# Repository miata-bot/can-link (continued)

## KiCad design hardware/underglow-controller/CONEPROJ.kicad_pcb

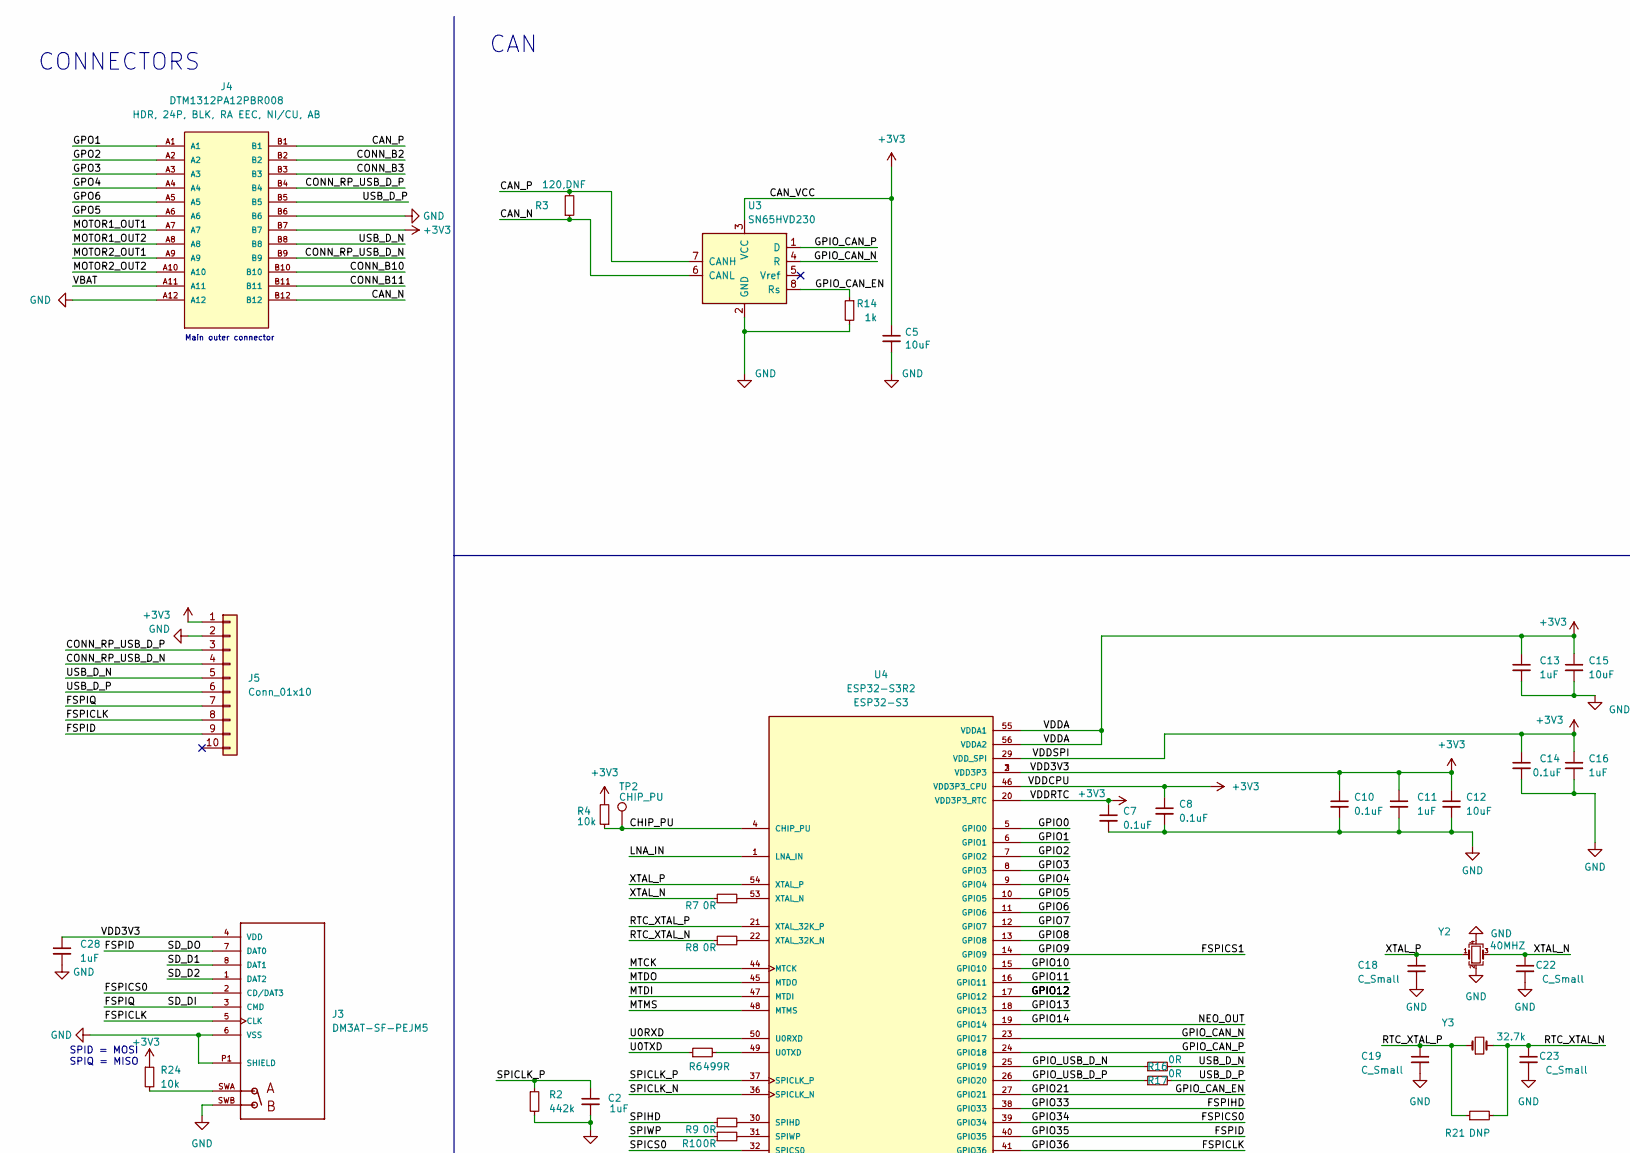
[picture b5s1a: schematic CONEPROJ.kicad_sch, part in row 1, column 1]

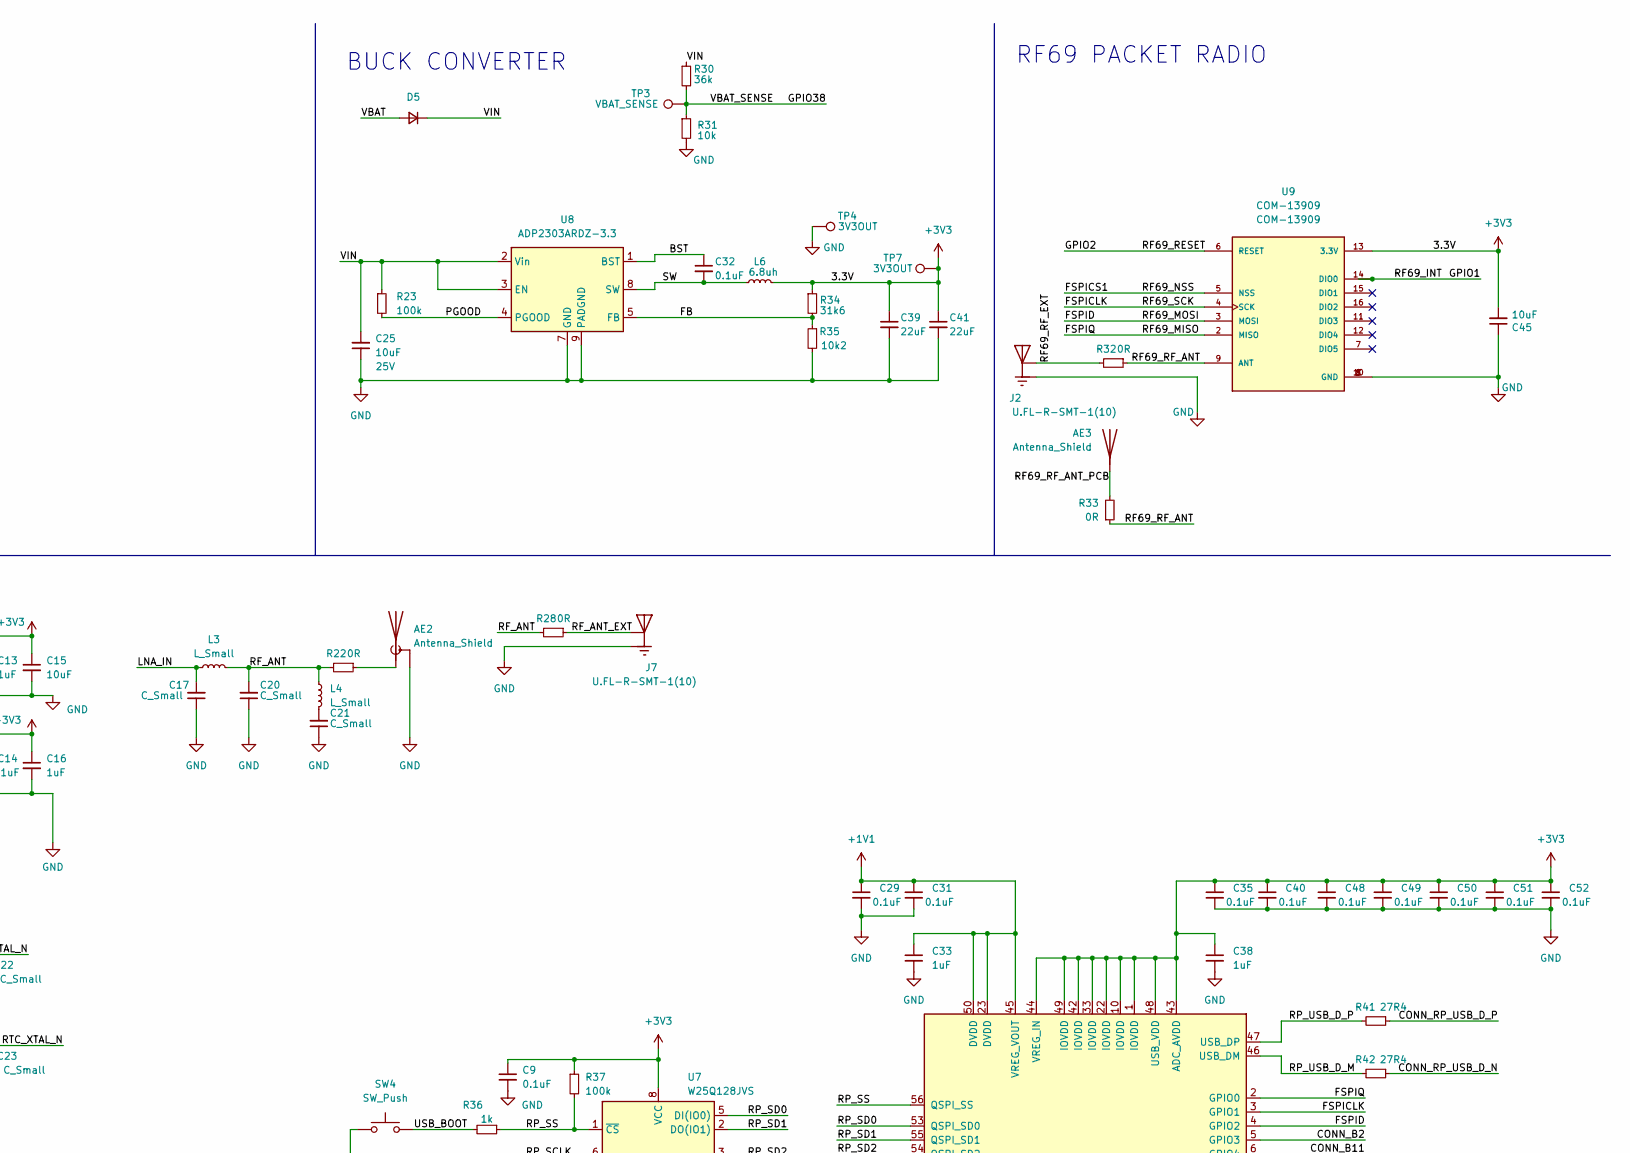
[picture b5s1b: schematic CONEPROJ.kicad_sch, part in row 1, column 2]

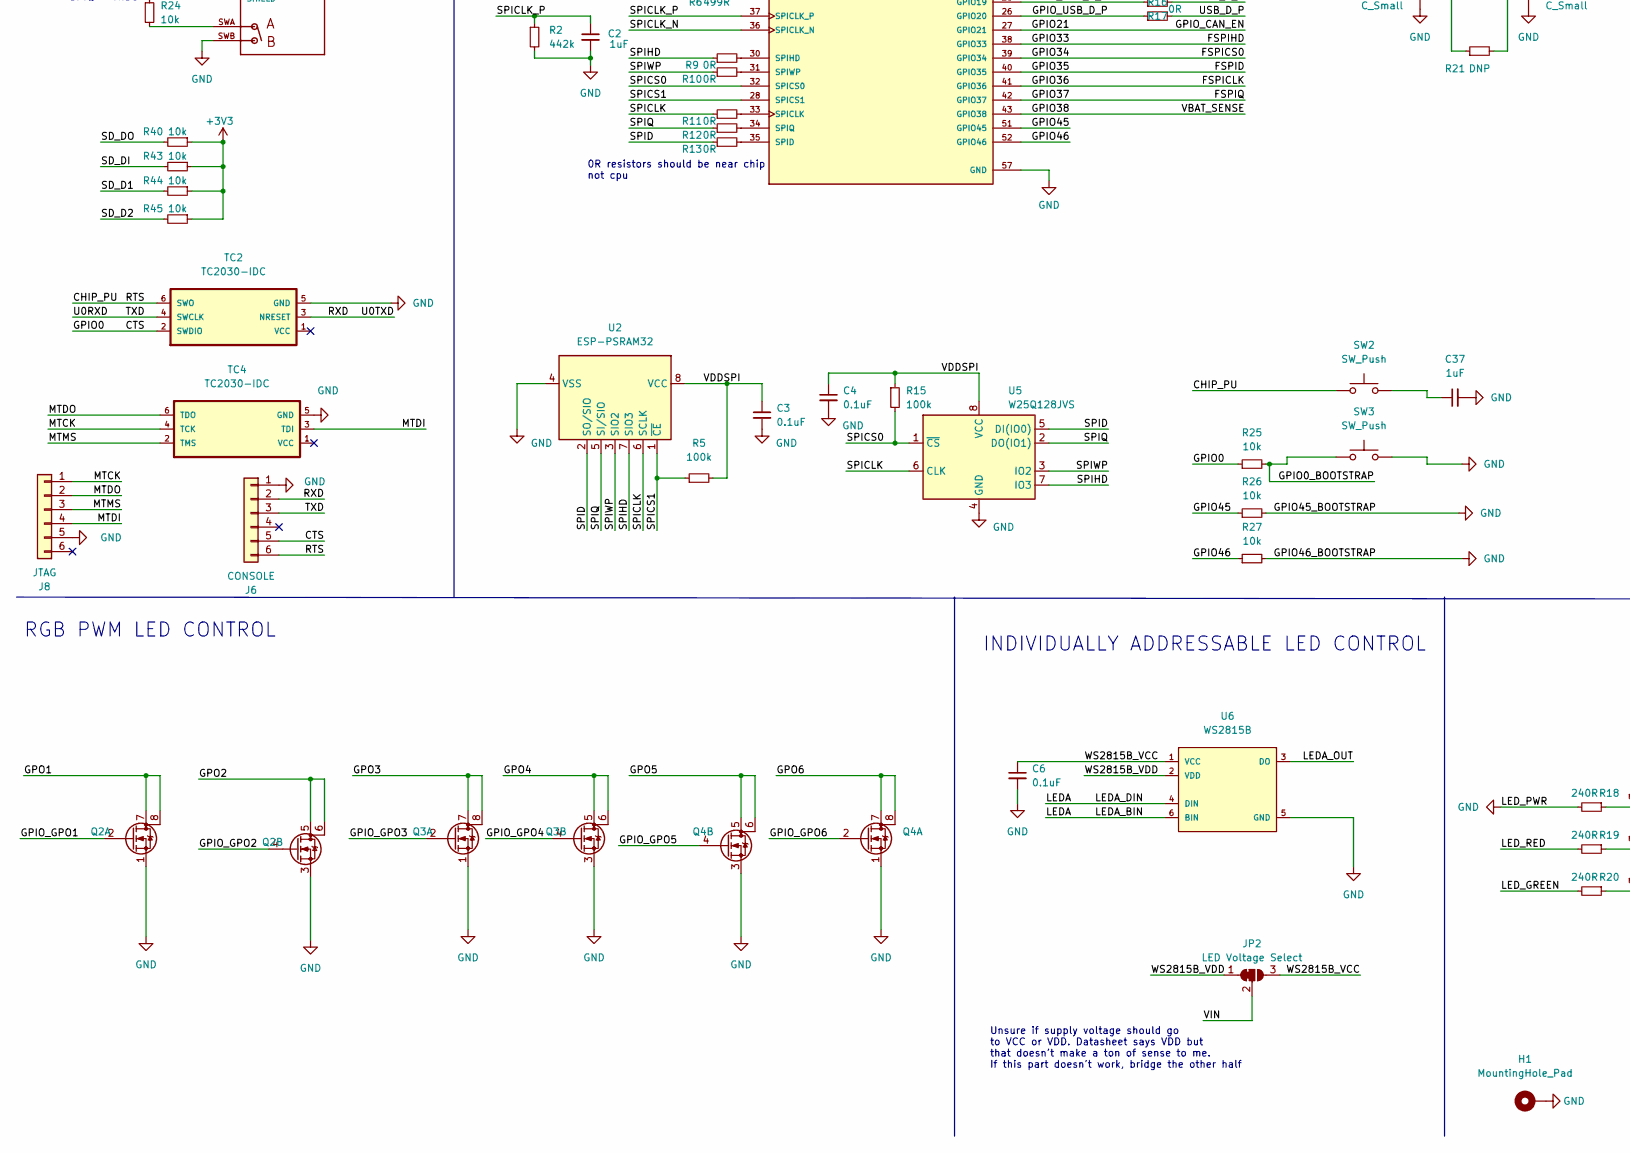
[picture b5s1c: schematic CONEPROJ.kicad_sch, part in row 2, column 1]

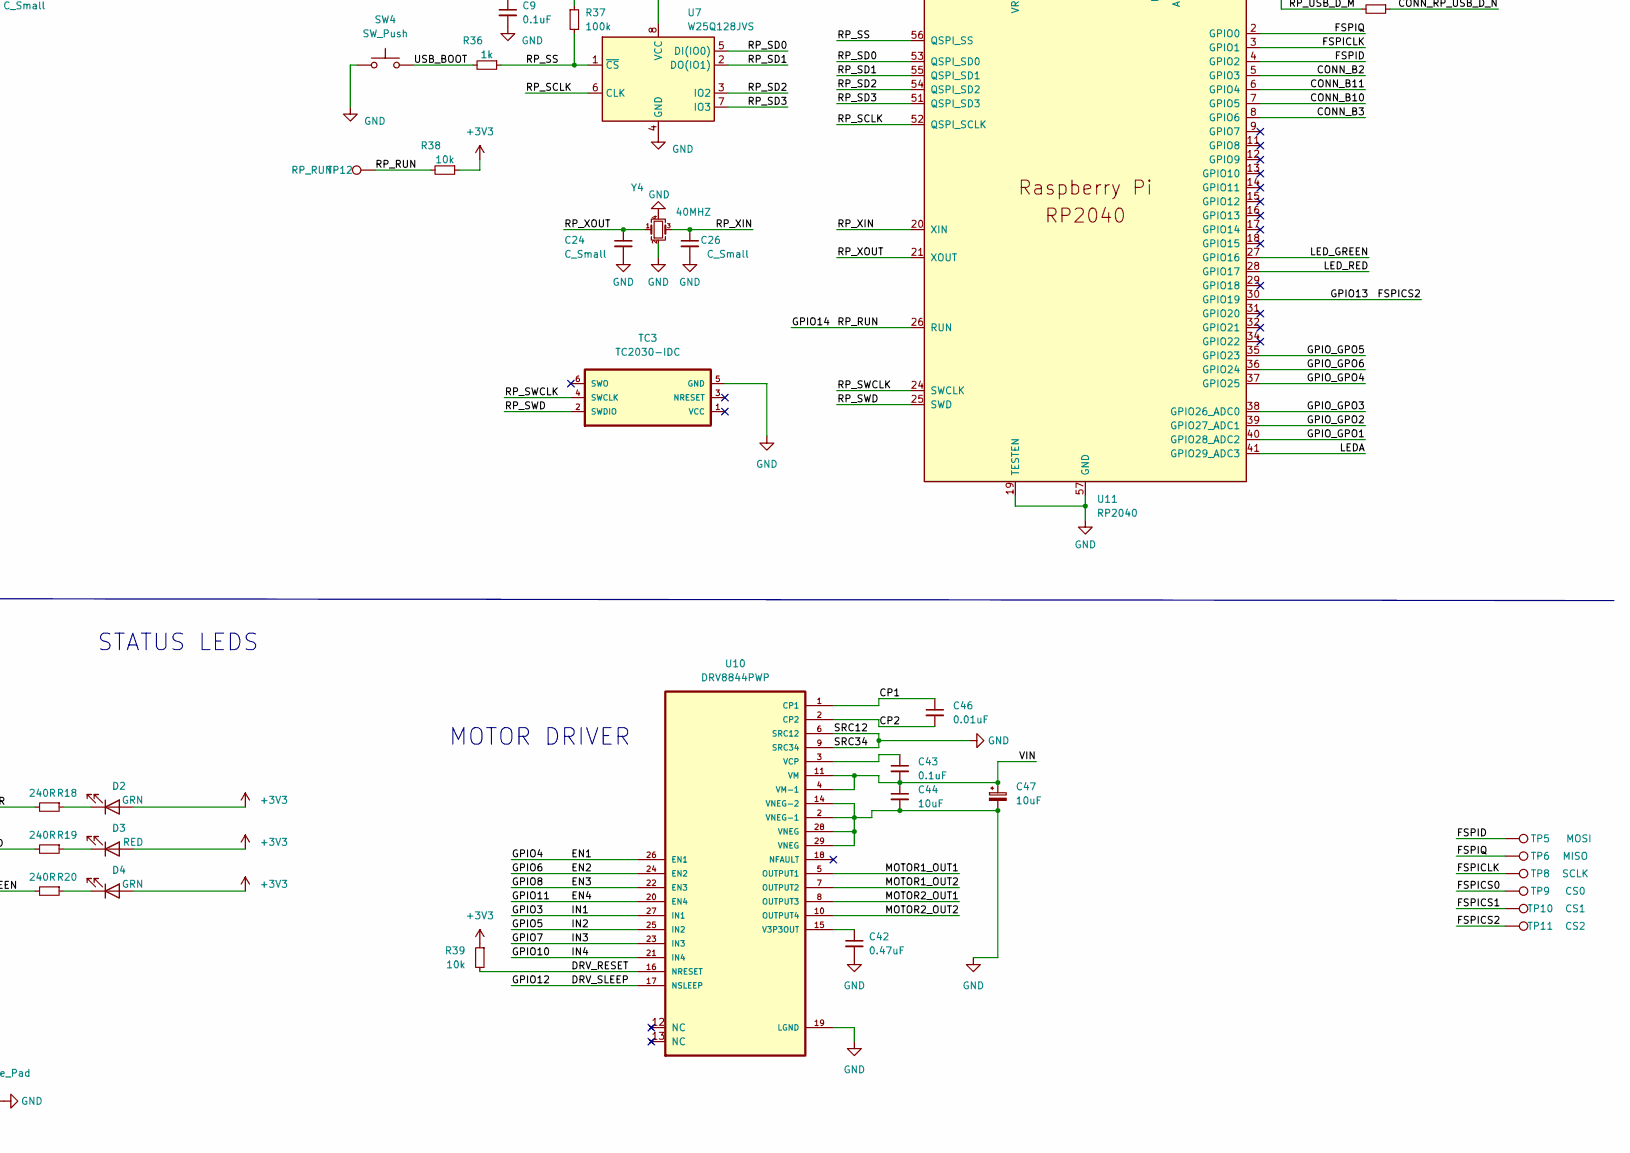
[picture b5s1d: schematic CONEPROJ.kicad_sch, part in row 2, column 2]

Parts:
AE2: Antenna_Shield; Texas_SWRA117D_2.4GHz_Right
AE3: Antenna_Shield; Texas_SWRA416_868MHz_915MHz
C2, C11, C13, C16, C28, C33, C37, C38: 1uF; C_0402_1005Metric
C3, C4, C7, C8, C9, C10, C14, C29, C31, C35, C40, C48, C49, C50, C51, C52: 0.1uF; C_0402_1005Metric
C5, C45: 10uF; C_0805_2012Metric; MPN2 CC0402KRX5R8BB104
C6, C32, C43: 0.1uF; C_0805_2012Metric
C12, C15: 10uF; C_0402_1005Metric
C17, C18, C19, C20, C21, C22, C23, C24, C26: C_Small; C_0402_1005Metric
C25: 10uF; C_0805_2012Metric; VOLTAGE 25V
C39, C41: 22uF; C_0805_2012Metric
C42: 0.47uF; C_0805_2012Metric
C44: 10uF; C_0805_2012Metric
C46: 0.01uF; C_0805_2012Metric
C47: 10uF; CP_Elec_5x5.3
D2, D4: GRN; LED_0603_1608Metric
D3: RED; LED_0603_1608Metric
D5: D_Small; D_SOD-123; MPN PMEG3015EH,115
H1: MountingHole_Pad; MountingHole_3.2mm_M3_DIN965_Pad
J2, J7: U.FL-R-SMT-1(10); HRS_U.FL-R-SMT-1(10); MPN U.FL-R-SMT-1(10)
J3: DM3AT-SF-PEJM5; HRS_DM3AT-SF-PEJM5; MPN DM3AT-SF-PEJM5
J4: DTM1312PA12PBR008; TE_DTM1312PA12PBR008; MPN DTM1312PA12PBR008
J5: Conn_01x10; PinHeader_1x10_P2.54mm_Vertical
J6: CONSOLE; PinHeader_1x06_P1.27mm_Vertical
J8: JTAG; PinHeader_1x06_P1.27mm_Vertical
JP2: LED Voltage Select; SolderJumper-3_P1.3mm_Bridged12_RoundedPad1.0x1.5mm_NumberL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
L3, L4: L_Small; L_0402_1005Metric
L6: 6.8uh; L_Bourns-SRN6028; MPN SRN6028-6R8M
Q2, Q3, Q4: Q_Dual_NMOS_S1G1S2G2D2D2D1D1; SO-8_3.9x4.9mm_P1.27mm; MPN STS8DNF3LL
R2: 442k; R_0402_1005Metric
R3: 120,DNF; R_0805_2012Metric
R4, R24, R25, R26, R27, R31, R38, R40, R43, R44, R45: 10k; R_0402_1005Metric
R5, R15, R37: 100k; R_0402_1005Metric
R6: 499R; R_0402_1005Metric
R7, R8, R9, R10, R11, R12, R13, R16, R17, R22, R28, R32, R33: 0R; R_0402_1005Metric
R14, R36: 1k; R_0402_1005Metric
R18, R19, R20: 240R; R_0603_1608Metric
R21: DNP; R_0402_1005Metric
R23: 100k; R_0603_1608Metric
R30: 36k; R_0402_1005Metric
R34: 31k6; R_0603_1608Metric
R35: 10k2; R_0603_1608Metric
R39: 10k; R_0603_1608Metric; MPN RMCF0603JT10K0
R41, R42: 27R4; R_0402_1005Metric
SW2, SW3, SW4: SW_Push; SW_RS-032G05A3-SMRT
TC2, TC3, TC4: TC2030-IDC; Tag-Connect_TC2030-IDC-NL_2x03_P1.27mm_Vertical
TP2: CHIP_PU; TestPoint_Pad_D1.0mm
TP3: VBAT_SENSE; TestPoint_Pad_D1.0mm
TP4, TP7: 3V3OUT; TestPoint_Pad_D1.0mm
TP5: MOSI; TestPoint_Pad_D1.0mm
TP6: MISO; TestPoint_Pad_D1.0mm
TP8: SCLK; TestPoint_Pad_D1.0mm
TP9: CS0; TestPoint_Pad_D1.0mm
TP10: CS1; TestPoint_Pad_D1.0mm
TP11: CS2; TestPoint_Pad_D1.0mm
TP12: RP_RUN; TestPoint_Pad_D1.0mm
U2: ESP-PSRAM32; SOIC-8_3.9x4.9mm_P1.27mm
U3: SN65HVD230; SOIC-8_3.9x4.9mm_P1.27mm; MPN SN65HVD230D
U4: ESP32-S3R2; QFN-56; MPN ESP32-S3
U5, U7: W25Q128JVS; SOIC-8_5.23x5.23mm_P1.27mm
U6: WS2815B; worldsemi-WS2815B-MFG
U8: ADP2303ARDZ-3.3; SOIC-8-1EP_3.9x4.9mm_P1.27mm_EP2.29x3mm
U9: COM-13909; XCVR_RFM69HW; MPN RFM69HCW
U10: DRV8844PWP; HTSSOP-28-1EP_4.4x9.7mm_P0.65mm_EP2.85x5.4mm_ThermalVias; MPN DRV8844PWP
U11: RP2040; QFN-56
Y2, Y4: 40MHZ; Crystal_SMD_3225-4Pin_3.2x2.5mm; MPN ECS-400-10-37B2-CKY-TR
Y3: 32.7k; Crystal_SMD_MicroCrystal_CC7V-T1A-2Pin_3.2x1.5mm

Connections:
+1V1: C29.1, C31.1, C33.1, U11.23 (DVDD), U11.45 (VREG_VOUT), U11.50 (DVDD)
+3V3: C3.1, C4.1, C5.1, C7.1, C8.1, C9.1, C10.1, C11.1, C12.1, C13.1, C14.1, C15.1, C16.1, C28.1, C35.1, C38.1, C39.1, C40.1, C41.1, C45.2, C48.1, C49.1, C50.1, C51.1, C52.1, D2.2 (A), D3.2 (A), D4.2 (A), J3.4 (VDD), J4.B7, J5.1, L6.2, R4.2, R5.2, R15.1, R24.1, R34.1, R37.1, R38.1, R39.1, R40.1, R43.1, R44.1, R45.1, TP7.1, U2.8 (VCC), U3.3 (VCC), U4.2 (VDD3P3), U4.3 (VDD3P3), U4.20 (VDD3P3_RTC), U4.29 (VDD_SPI), U4.46 (VDD3P3_CPU), U4.55 (VDDA1), U4.56 (VDDA2), U5.8 (VCC), U7.8 (VCC), U9.13 (3.3V), U11.1 (IOVDD), U11.10 (IOVDD), U11.22 (IOVDD), U11.33 (IOVDD), U11.42 (IOVDD), U11.43 (ADC_AVDD), U11.44 (VREG_IN), U11.48 (USB_VDD), U11.49 (IOVDD)
/BST: C32.1, U8.1 (BST)
/CAN_N: J4.B12, R3.1, U3.6 (CANL)
/CAN_P: J4.B1, R3.2, U3.7 (CANH)
/CHIP_PU: J6.6, R4.1, SW2.1, TC2.6 (SWO), TP2.1, U4.4 (CHIP_PU)
/CONN_B2: J4.B2, U11.5 (GPIO3)
/CONN_B3: J4.B3, U11.8 (GPIO6)
/CONN_B10: J4.B10, U11.7 (GPIO5)
/CONN_B11: J4.B11, U11.6 (GPIO4)
/CONN_RP_USB_D_N: J4.B9, J5.4, R42.1
/CONN_RP_USB_D_P: J4.B4, J5.3, R41.1
/CP1: C46.1, U10.1 (CP1)
/CTS: J6.5, R25.1, TC2.2 (SWDIO), U4.5 (GPIO0)
/DRV_RESET: R39.2, U10.16 (NRESET)
/DRV_SLEEP: U4.17 (GPIO12), U10.17 (NSLEEP)
/EN1: U4.9 (GPIO4), U10.26 (EN1)
/EN2: U4.11 (GPIO6), U10.24 (EN2)
/EN3: U4.13 (GPIO8), U10.22 (EN3)
/EN4: U4.16 (GPIO11), U10.20 (EN4)
/FB: R34.2, R35.1, U8.5 (FB)
/FSPICLK: J3.5 (CLK), J5.8, TP8.1, U4.41 (GPIO36), U9.4 (SCK), U11.3 (GPIO1)
/FSPICS0: J3.2 (CD/DAT3), TP9.1, U4.39 (GPIO34)
/FSPICS1: TP10.1, U4.14 (GPIO9), U9.5 (NSS)
/FSPICS2: TP11.1, U4.18 (GPIO13), U11.30 (GPIO19)
/FSPID: J3.7 (DAT0), J5.9, R40.2, TP5.1, U4.40 (GPIO35), U9.3 (MOSI), U11.4 (GPIO2)
/FSPIHD: U4.38 (GPIO33)
/FSPIQ: J3.3 (CMD), J5.7, R43.2, TP6.1, U4.42 (GPIO37), U9.2 (MISO), U11.2 (GPIO0)
/GPIO0_BOOTSTRAP: R25.2, SW3.1
/GPIO1: U4.6 (GPIO1), U9.14 (DIO0)
/GPIO2: U4.7 (GPIO2), U9.6 (RESET)
/GPIO3: U4.8 (GPIO3), U10.27 (IN1)
/GPIO5: U4.10 (GPIO5), U10.25 (IN2)
/GPIO7: U4.12 (GPIO7), U10.23 (IN3)
/GPIO10: U4.15 (GPIO10), U10.21 (IN4)
/GPIO14: R38.2, TP12.1, U4.19 (GPIO14), U11.26 (RUN)
/GPIO21: R14.1, U3.8 (Rs), U4.27 (GPIO21)
/GPIO38: R30.2, R31.1, TP3.1, U4.43 (GPIO38)
/GPIO45: R26.1, U4.51 (GPIO45)
/GPIO46: R27.1, U4.52 (GPIO46)
/GPIO_CAN_N: U3.4 (R), U4.23 (GPIO17)
/GPIO_CAN_P: U3.1 (D), U4.24 (GPIO18)
/GPIO_GPO1: Q2.2 (G), U11.40 (GPIO28_ADC2)
/GPIO_GPO2: Q2.4 (G), U11.39 (GPIO27_ADC1)
/GPIO_GPO3: Q3.2 (G), U11.38 (GPIO26_ADC0)
/GPIO_GPO4: Q3.4 (G), U11.37 (GPIO25)
/GPIO_GPO5: Q4.4 (G), U11.35 (GPIO23)
/GPIO_GPO6: Q4.2 (G), U11.36 (GPIO24)
/GPIO_USB_D_N: R16.1, U4.25 (GPIO19)
/GPIO_USB_D_P: R17.1, U4.26 (GPIO20)
/GPO1: J4.A1, Q2.7 (D), Q2.8 (D)
/GPO2: J4.A2, Q2.5 (D), Q2.6 (D)
/GPO3: J4.A3, Q3.7 (D), Q3.8 (D)
/GPO4: J4.A4, Q3.5 (D), Q3.6 (D)
/GPO5: J4.A6, Q4.5 (D), Q4.6 (D)
/GPO6: J4.A5, Q4.7 (D), Q4.8 (D)
/LEDA: U6.4 (DIN), U6.6 (BIN), U11.41 (GPIO29_ADC3)
/LEDA_OUT: U6.3 (DO)
/LED_GREEN: R20.2, U11.27 (GPIO16)
/LED_RED: R19.2, U11.28 (GPIO17)
/LNA_IN: C17.2, L3.1, U4.1 (LNA_IN)
/MOTOR1_OUT1: J4.A7, U10.5 (OUTPUT1)
/MOTOR1_OUT2: J4.A8, U10.7 (OUTPUT2)
/MOTOR2_OUT1: J4.A9, U10.8 (OUTPUT3)
/MOTOR2_OUT2: J4.A10, U10.10 (OUTPUT4)
/MTCK: J8.1, TC4.4 (TCK), U4.44 (MTCK)
/MTDI: J8.4, TC4.3 (TDI), U4.47 (MTDI)
/MTDO: J8.2, TC4.6 (TDO), U4.45 (MTDO)
/MTMS: J8.3, TC4.2 (TMS), U4.48 (MTMS)
/PGOOD: R23.2, U8.4 (PGOOD)
/RF69_RF_ANT: R32.1, R33.1, U9.9 (ANT)
/RF69_RF_ANT_PCB: AE3.1 (A), R33.2
/RF69_RF_EXT: J2.2, R32.2
/RF_ANT: C20.2, L3.2, L4.1, R22.2, R28.2
/RF_ANT_EXT: J7.2, R28.1
/RP_SCLK: U7.6 (CLK), U11.52 (QSPI_SCLK)
/RP_SD0: U7.5 (DI(IO0)), U11.53 (QSPI_SD0)
/RP_SD1: U7.2 (DO(IO1)), U11.55 (QSPI_SD1)
/RP_SD2: U7.3 (IO2), U11.54 (QSPI_SD2)
/RP_SD3: U7.7 (IO3), U11.51 (QSPI_SD3)
/RP_SS: R36.1, R37.2, U7.1 (~CS), U11.56 (QSPI_SS)
/RP_SWCLK: TC3.4 (SWCLK), U11.24 (SWCLK)
/RP_SWD: TC3.2 (SWDIO), U11.25 (SWD)
/RP_USB_D_M: R42.2, U11.46 (USB_DM)
/RP_USB_D_P: R41.2, U11.47 (USB_DP)
/RP_XIN: C26.1, U11.20 (XIN), Y4.3
/RP_XOUT: C24.1, U11.21 (XOUT), Y4.1
/RTC_XTAL_N: C23.1, R8.1, R21.2, Y3.2
/RTC_XTAL_P: C19.1, R21.1, U4.21 (XTAL_32K_P), Y3.1
/RXD: J6.2, R6.1, TC2.3 (NRESET)
/SD_D1: J3.8 (DAT1), R44.2
/SD_D2: J3.1 (DAT2), R45.2
/SPICLK: R11.1, U2.6 (SCLK), U5.6 (CLK)
/SPICLK_N: U4.36 (SPICLK_N)
/SPICLK_P: C2.1, R2.1, U4.37 (SPICLK_P)
/SPICS0: R15.2, U4.32 (SPICS0), U5.1 (~CS)
/SPICS1: R5.1, U2.1 (~CE), U4.28 (SPICS1)
/SPID: R13.1, U2.2 (SO/SIO), U5.5 (DI(IO0))
/SPIHD: R9.1, U2.7 (SIO3), U5.7 (IO3)
/SPIQ: R12.1, U2.5 (SI/SIO), U5.2 (DO(IO1))
/SPIWP: R10.1, U2.3 (SIO2), U5.3 (IO2)
/SW: C32.2, L6.1, U8.8 (SW)
/TXD: J6.3, TC2.4 (SWCLK), U4.50 (U0RXD)
/USB_BOOT: R36.2, SW4.2
/USB_D_N: J4.B8, J5.5, R16.2
/USB_D_P: J4.B5, J5.6, R17.2
/VBAT: D5.2 (A), J4.A11
/VIN: C25.2, C43.2, C44.1, C47.1, D5.1 (K), JP2.2 (C), R23.1, R30.1, U8.2 (Vin), U8.3 (EN), U10.4 (VM-1), U10.11 (VM)
/WS2815B_VCC: C6.1, JP2.3 (B), U6.1 (VCC)
/WS2815B_VDD: JP2.1 (A), U6.2 (VDD)
/XTAL_N: C22.1, R7.1, Y2.3
/XTAL_P: C18.1, U4.54 (XTAL_P), Y2.1
unnamed: AE2.1 (A), R22.1
unnamed: C21.2, L4.2
unnamed: C37.1, SW2.2
unnamed: C42.1, U10.15 (V3P3OUT)
unnamed: C43.1, U10.3 (VCP)
unnamed: D2.1 (K), R18.1
unnamed: D3.1 (K), R19.1
unnamed: D4.1 (K), R20.1
unnamed: R6.2, U4.49 (U0TXD)
unnamed: R7.2, U4.53 (XTAL_N)
unnamed: R8.2, U4.22 (XTAL_32K_N)
unnamed: R9.2, U4.30 (SPIHD)
unnamed: R10.2, U4.31 (SPIWP)
unnamed: R11.2, U4.33 (SPICLK)
unnamed: R12.2, U4.34 (SPIQ)
unnamed: R13.2, U4.35 (SPID)
unnamed: J3.SWA, R24.2

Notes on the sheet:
Unsure if supply voltage should go to VCC or VDD. Datasheet says VDD but that doesn't make a ton of sense to me. If this part doesn't work, bridge the other half
CAN
Main outer connector
INDIVIDUALLY ADDRESSABLE LED CONTROL
0R resistors should be near chip not cpu
CONNECTORS
SPID = MOSI SPIQ = MISO
STATUS LEDS
BUCK CONVERTER
MOTOR DRIVER
RF69 PACKET RADIO
RGB PWM LED CONTROL

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
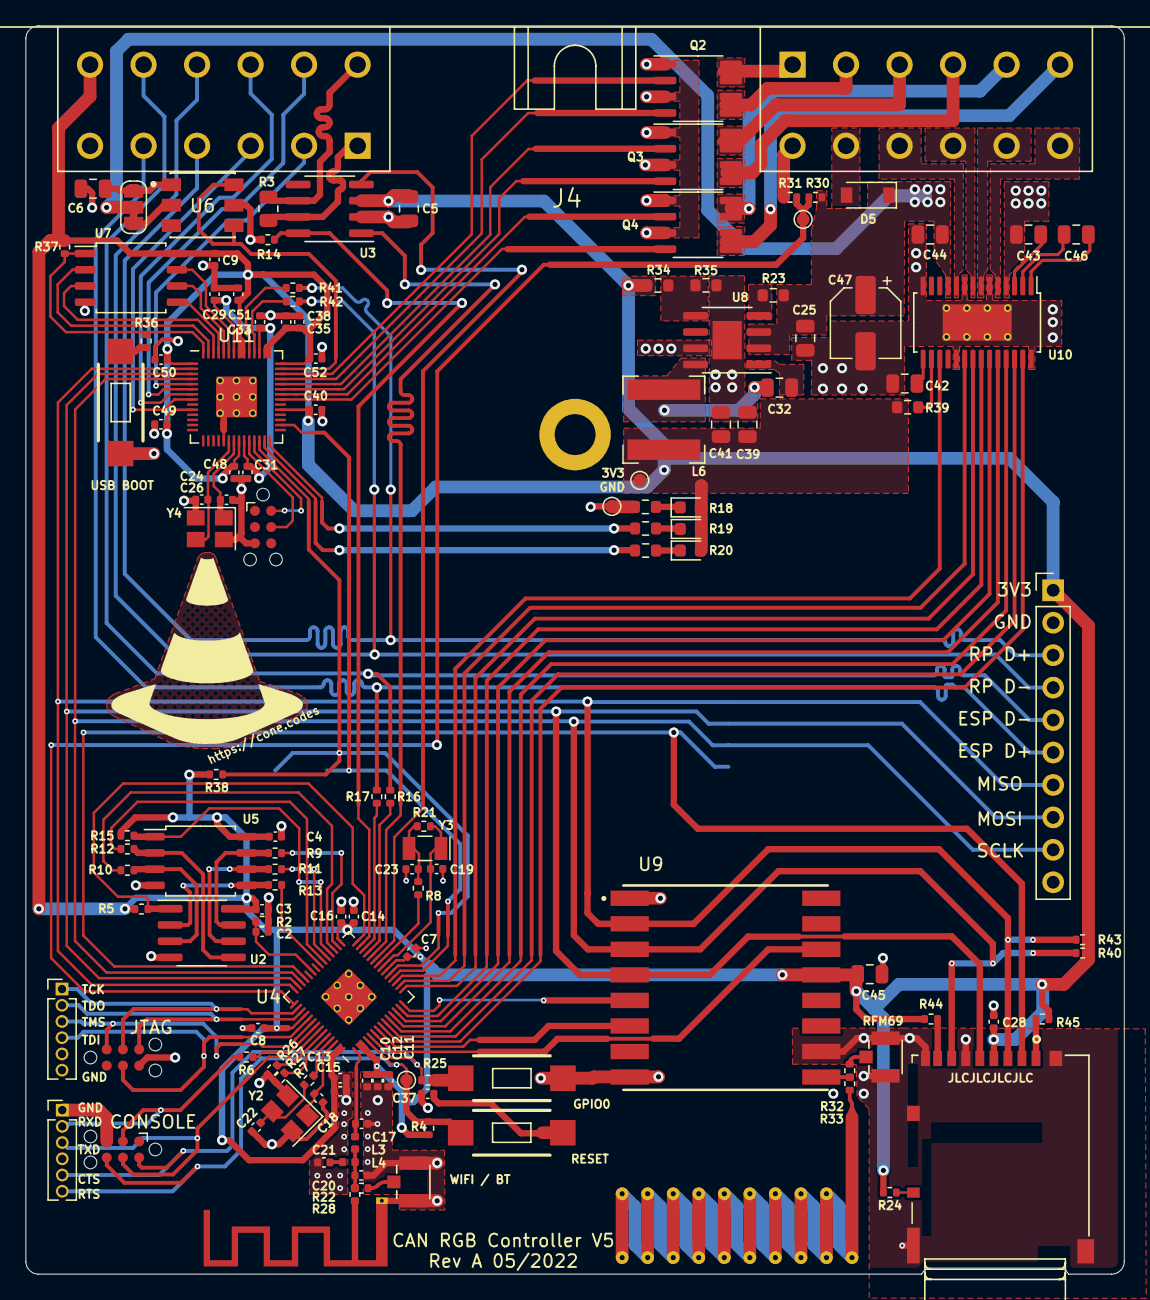
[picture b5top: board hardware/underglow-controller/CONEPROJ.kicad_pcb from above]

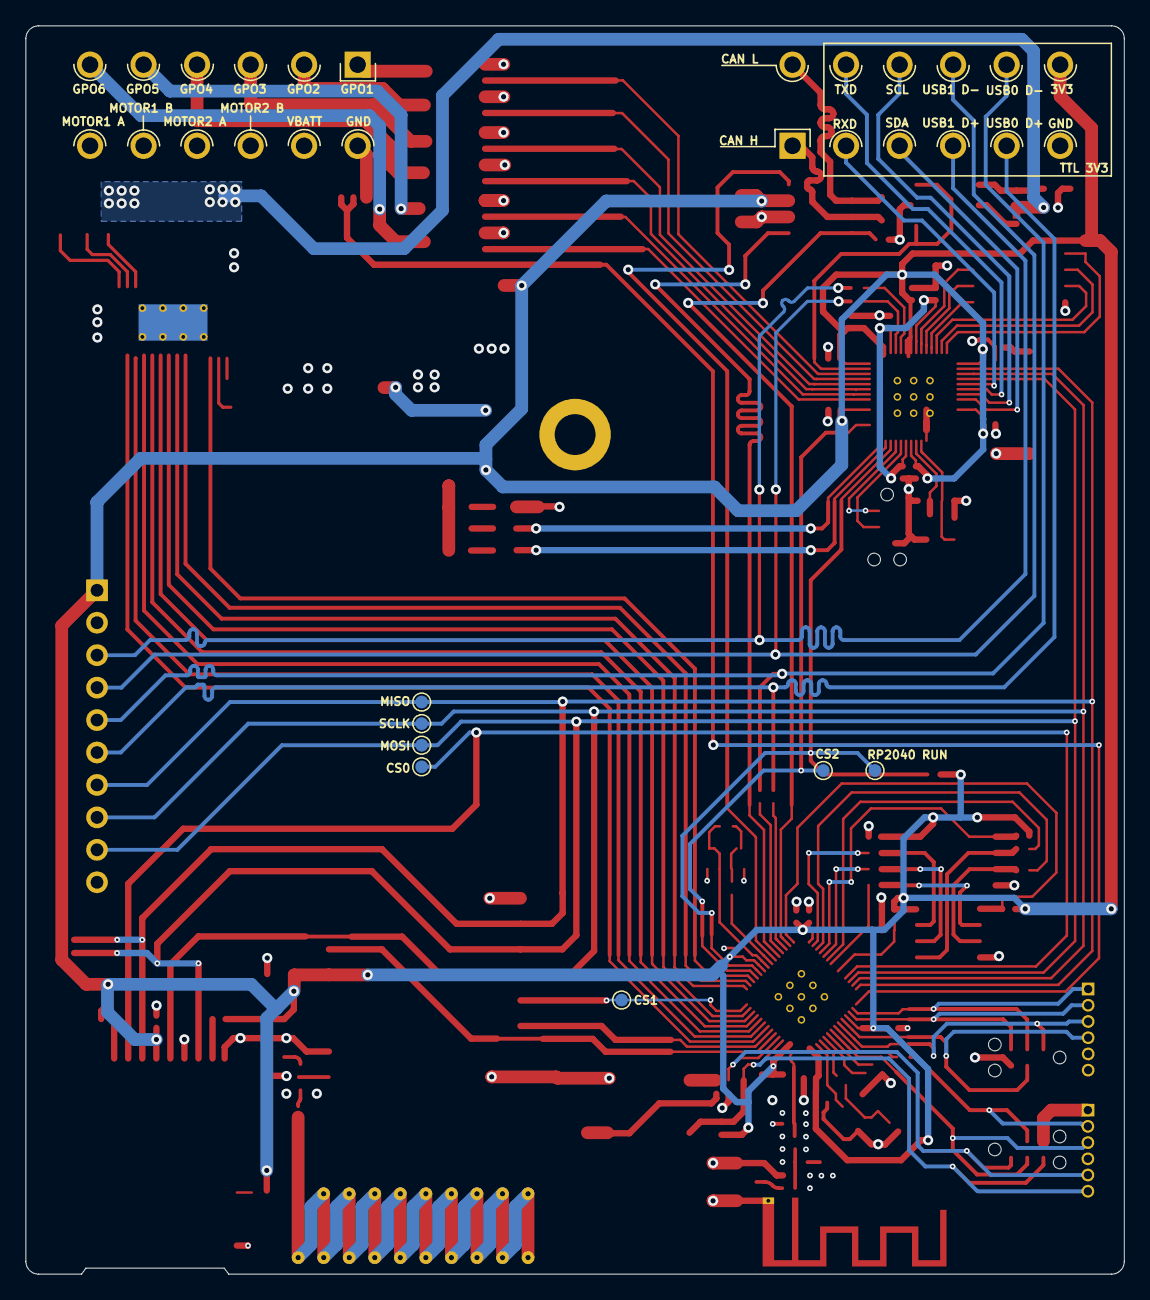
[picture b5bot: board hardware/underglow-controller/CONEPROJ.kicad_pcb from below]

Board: 4 copper layers, 86.0 x 97.7 mm, 141 parts (7 on the bottom side), 128 nets.

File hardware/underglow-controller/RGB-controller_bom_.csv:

Component,Description,Part,References,Value,Footprint,Quantity Per PCB,Datasheet,MPN,LCSC,MPN2
1,"Unpolarized capacitor, small symbol",C_Small,C21,2pF,C_0402_1005Metric,1,~,04023J2R0ABSTR,,
2,"Unpolarized capacitor, small symbol",C_Small,C20,4pF,C_0402_1005Metric,1,~,04025J4R0ABSTR,,
3,"Unpolarized capacitor, small symbol",C_Small,C17,4.6pF,C_0402_1005Metric,1,~,04023J4R6ABSTR,,
4,"Unpolarized capacitor, small symbol",C_Small,C19 C23,10pF,C_0402_1005Metric,2,~,C0402C100K5RACAUTO,,
5,"Unpolarized capacitor, small symbol",C_Small,C18 C22,16pF,C_0402_1005Metric,2,~,04025A160JAT2A,,
6,"Unpolarized capacitor, small symbol",C_Small,C24 C26,20pF,C_0402_1005Metric,2,~,06035A200JAT2A,,
7,"Unpolarized capacitor, small symbol",C_Small,C46,0.01uF,C_0805_2012Metric,1,~,C0805C103J3GACAUTO,,
8,"Unpolarized capacitor, small symbol",C_Small,C4 C7 C8 C9 C10 C14 C29 C31 C35 C40 C48 C49 C50 C51 C52,0.1uF,C_0402_1005Metric,15,~,04023C104KAT4A,,
9,"Unpolarized capacitor, small symbol",C_Small,C6 C32 C43,0.1uF,C_0805_2012Metric,3,~,08055C104M4T4A,,
10,"Unpolarized capacitor, small symbol",C_Small,C42,0.47uF,C_0805_2012Metric,1,~,0805ZC474MAT2A,,
11,"Unpolarized capacitor, small symbol",C_Small,C11 C13 C16 C28 C33 C37 C38,1uF,C_0402_1005Metric,7,~,04023D105KAT2A,,
12,"Unpolarized capacitor, small symbol",C_Small,C12 C15,10uF,C_0402_1005Metric,2,~,04026D106MAT2A,,
13,"Unpolarized capacitor, small symbol",C_Small,C5 C25 C44 C45,10uF,C_0805_2012Metric,4,~,0805YC106KAT2A,,
14,"Polarized capacitor, small symbol",C_Polarized_Small,C47,10uF,CP_Elec_5x5.3,1,~,EDH106M050A9DAA,,
15,"Unpolarized capacitor, small symbol",C_Small,C39 C41,22uF,C_0805_2012Metric,2,~,08056D226MAT2A,,
16,"Diode, small symbol",D_Small,D5,D_Small,D_SOD-123F,1,~,RB070MM-30TR,,
17,Light emitting diode,LED,D2 D4,GRN,LED_0603_1608Metric,2,~,150060VS75000,,
18,Light emitting diode,LED,D3,RED,LED_0603_1608Metric,1,~,150060SS75003,,
19,DM3 RA SMT microSD memory card push/push,DM3AT-SF-PEJM5,J3,DM3AT-SF-PEJM5,HRS_DM3AT-SF-PEJM5,1,https://www.mouser.com/datasheet/2/185/DM3AT_SF_PEJM5_CL0609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,DM3AT-SF-PEJM5,C114218,
20," HDR, 24P, BLK, RA EEC, NI/CU, AB",DTM1312PA12PBR008,J4,DTM1312PA12PBR008,TE_DTM1312PA12PBR008,1,https://www.te.com/usa-en/product-DTM1312PA12PBR008.datasheet.pdf,DTM1312PA12PBR008,,
21,"Inductor, small symbol",L_Small,L3,2nH,L_0402_1005Metric,1,~,MHQ0402PSA22NHT000,,
22,"Inductor, small symbol",L_Small,L4,2.2nH,L_0402_1005Metric,1,~,LCCI0402S2N2GTAR,,
23,"Inductor, small symbol",L_Small,L6,6.8uh,L_Bourns-SRN6028,1,https://www.bourns.com/docs/Product-Datasheets/SRN6028.pdf,SRN6028-6R8M,,
24,"Resistor, small symbol",R_Small,R7 R8 R9 R10 R11 R12 R13 R16 R17 R22 R28 R32 R33,0R,R_0402_1005Metric,13,~,AC0402JR-070RL,,
25,"Resistor, small symbol",R_Small,R41 R42,27r4,R_0402_1005Metric,2,~,CR0402-FX-27R4GLF,,
26,"Resistor, small symbol",R_Small,R18 R19 R20,240R,R_0603_1608Metric,3,~,,,
27,"Resistor, small symbol",R_Small,R6,499R,R_0402_1005Metric,1,~,RC0402FR-13499RL,,
28,"Resistor, small symbol",R_Small,R14 R36,1k,R_0402_1005Metric,2,~,RT0402FRE071KL,,
29,"Resistor, small symbol",R_Small,R23,10k,R_0603_1608Metric,1,~,RC0603FR-0710KL,,
30,"Resistor, small symbol",R_Small,R4 R24 R25 R26 R27 R31 R38 R39 R40 R43 R44 R45,10k,R_0402_1005Metric,12,~,RC0402FR-1010KL RC0603FR-0710KL,,
31,"Resistor, small symbol",R_Small,R35,10k2,R_0603_1608Metric,1,~,CR0603-FX-1022ELF,,
32,"Resistor, small symbol",R_Small,R34,31k6,R_0603_1608Metric,1,~,CR0603-FX-3162ELF,,
33,"Resistor, small symbol",R_Small,R30,36k,R_0402_1005Metric,1,~,AC0402JR-0736KL,,
34,"Resistor, small symbol",R_Small,R15 R37,100k,R_0402_1005Metric,2,~,AC0402FR-07100KL,,
35,"Resistor, small symbol",R_Small,R3,"120,DNF",R_0805_2012Metric,1,~,,,
36,"Push button switch, generic, two pins",SW_Push,SW2 SW3 SW4,SW_Push,SW_RS-032G05A3-SMRT,3,~,RS032G05A3SMRT,,
37,,TC2030-IDC,TC3,TC2030-IDC,Tag-Connect_TC2030-IDC-NL_2x03_P1.27mm_Vertical,1,,,,
38,RX TXRX MODULE ISM < 1GHZ SMD ,COM-13909,U9,COM-13909,XCVR_RFM69HW,1,https://cdn.sparkfun.com/datasheets/Wireless/General/RFM69HC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,RFM69HCW,,COM-13909
39,Motor / Motion / Ignition Controllers & Drivers Brushed DC motor Solenoid/Relay Drvr ,DRV8844PWP,U10,DRV8844PWP,HTSSOP-28-1EP_4.4x9.7mm_P0.65mm_EP2.85x5.4mm_ThermalVias,1,http://www.ti.com/general/docs/suppproductinfo.tsp?distId=26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,DRV8844PWP,C177807,
40,"SMD IC ESP32-S3, DUAL-CORE MCU,",ESP32-S3R2,U4,ESP32-S3R2,QFN-56,1,,ESP32-S3,C2913192,
41,,RP2040,U11,RP2040,QFN-56,1,https://datasheets.raspberrypi.com/rp2040/rp2040-datasheet.pdf,RP2040,C2040,
42,"128Mb Serial Flash Memory, Standard/Dual/Quad SPI, SOIC-8",W25Q128JVS,U7,W25Q128JVS,SOIC-8W_5.3x5.3mm_P1.27mm,1,http://www.winbond.com/resource-files/w25q128jv_dtr%20revc%2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,W25Q128JVS,C113767,
43,"Programmable LED; SMD; 5050,PLCC6; RGB; 5x5x1.6mm; 12V; -25÷85°C ",WS2815B,U6,WS2815B,worldsemi-WS2815B-MFG,1,http://www.world-semi.com/DownLoadFile/138,,C965559,
44,"Two pin crystal, small symbol",Crystal_Small,Y3,32.7k,Crystal_SMD_MicroCrystal_CC7V-T1A-2Pin_3.2x1.5mm,1,~,ABS07-32.768KHZ-7-T,,
45,"Four pin crystal, GND on pins 2 and 4, small symbol",Crystal_GND24_Small,Y2 Y4,40MHZ,Crystal_SMD_3225-4Pin_3.2x2.5mm,2,~,ECS-400-10-37B2-CKY-TR ABM8-12.000MHZ-12-B1U-T,,





Component Groups:,46
Component Count:,108
Fitted Components:,107
Number of PCBs:,1
Total components:,107
Schematic Version:,
Schematic Date:,
PCB Variant:,default
BoM Date:,Wed 18 May 2022 01:53:08 PM MDT
Schematic Source:,RGB-controller.kicad_sch
KiCad Version:,Eeschema (6.0.2)
